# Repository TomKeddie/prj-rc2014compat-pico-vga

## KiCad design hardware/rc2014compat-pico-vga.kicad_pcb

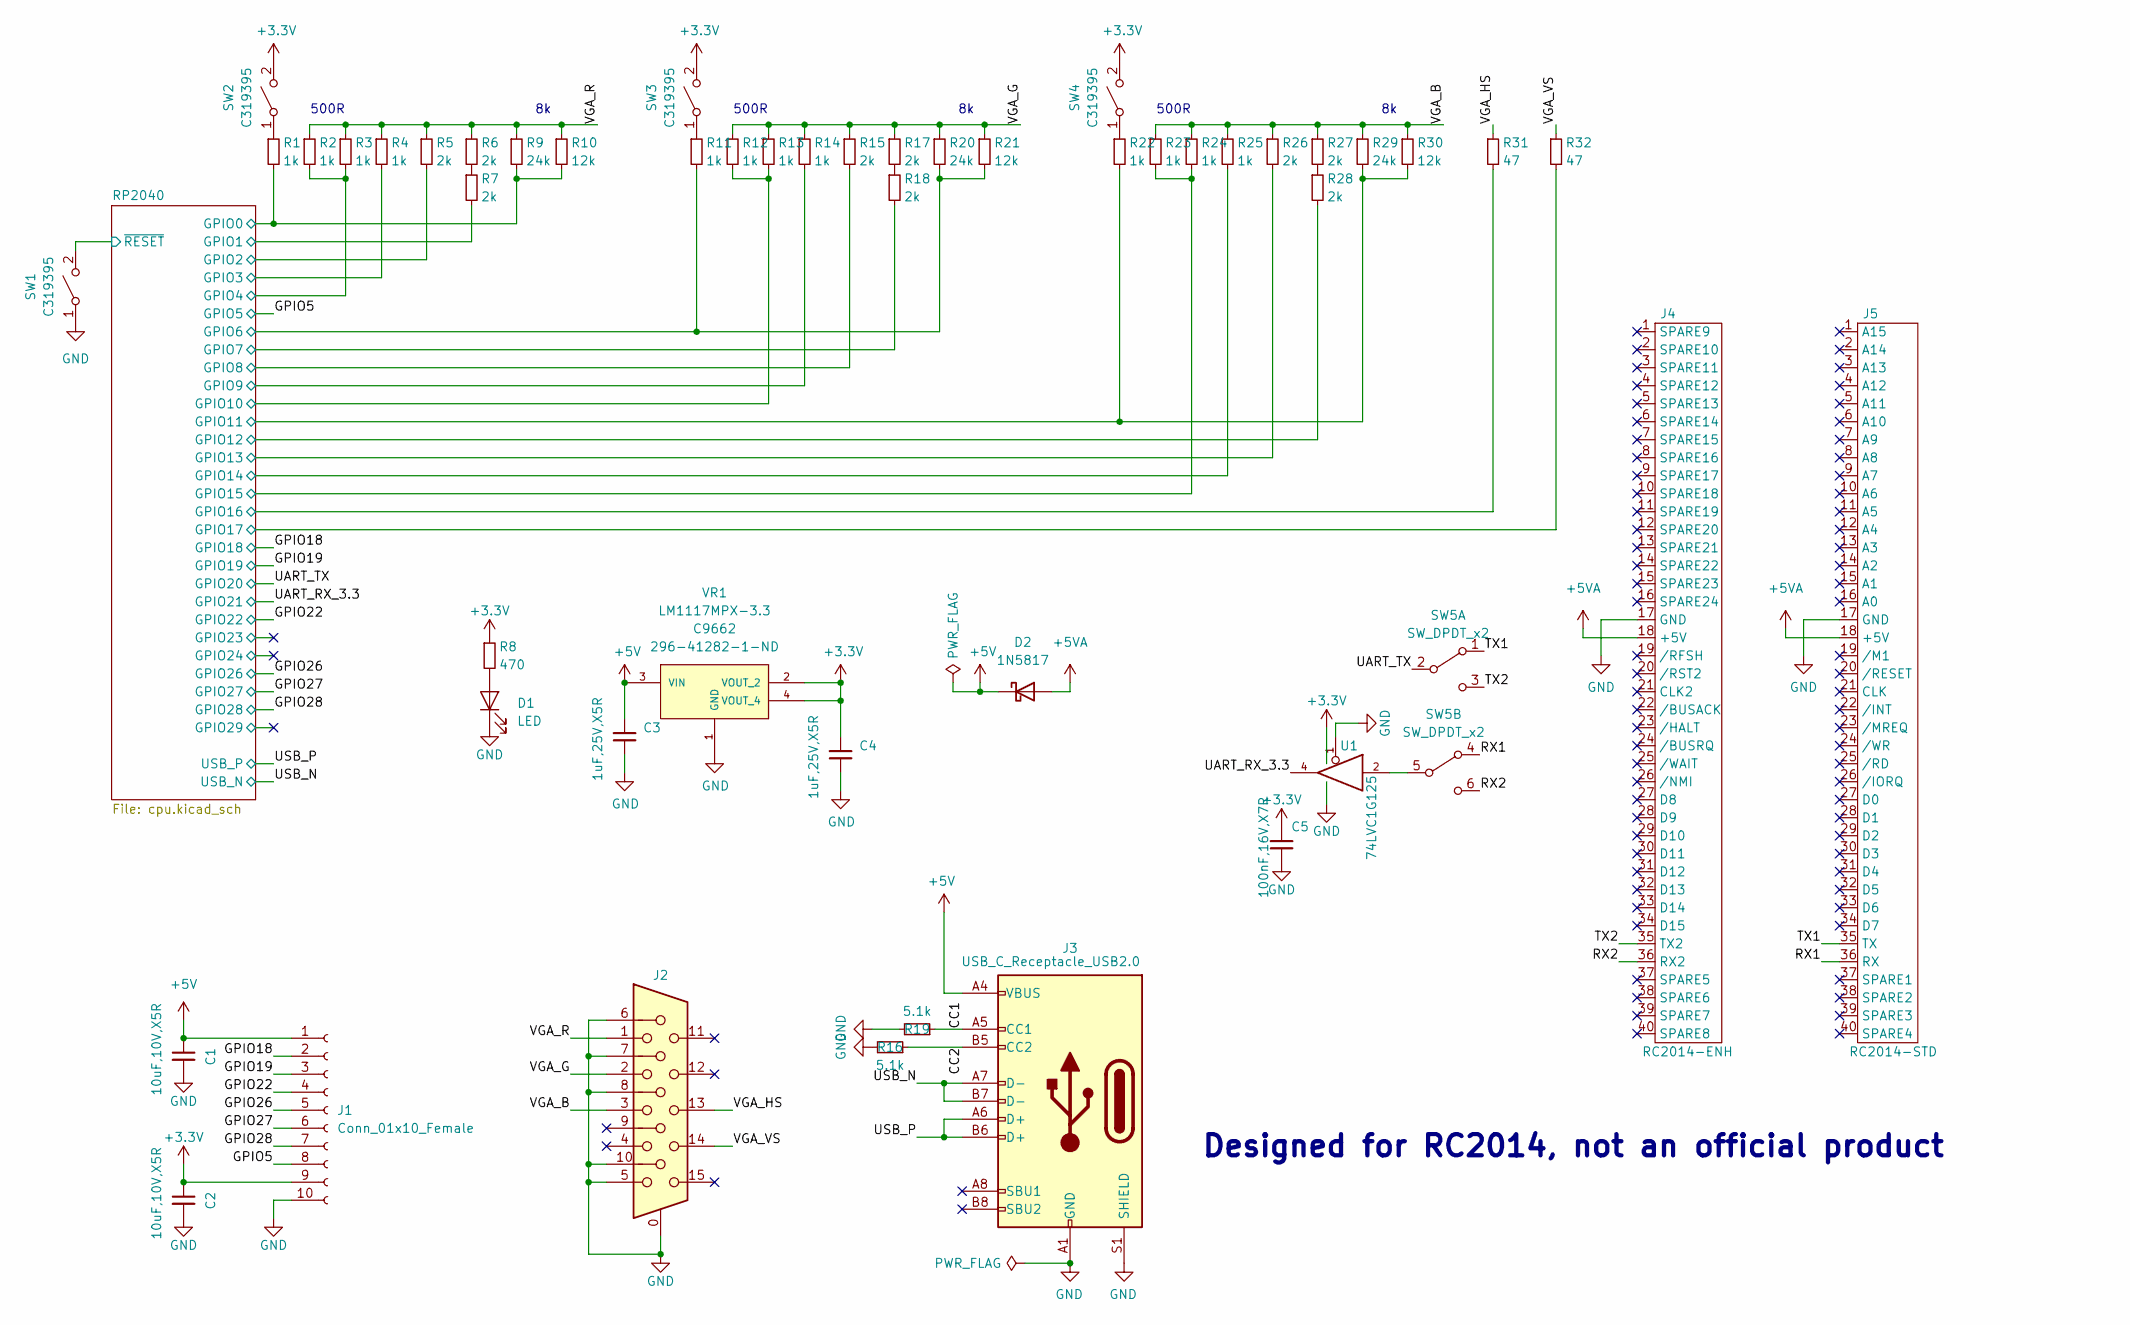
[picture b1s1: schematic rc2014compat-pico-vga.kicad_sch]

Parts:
C1, C2: 10uF,10V,X5R; C_0603_1608Metric; MFGPN CL10A106KP8NNNC; LCSC C19702
C3, C4: 1uF,25V,X5R; C_0402_1005Metric; MFGPN CL05A105KA5NQNC; LCSC C52923
C5: 100nF,16V,X7R; C_0402_1005Metric; MFGPN CL05B104KO5NNNC; LCSC C1525
D1: LED; LED_0603_1608Metric; LCSC C2286
D2: 1N5817; D_SOD-123; LCSC C727113
J1: Conn_01x10_Female; PinHeader_1x10_P2.54mm_Vertical
J2: DB15_Female_HighDensity_MountingHoles; DSUB-15-HD_Female_Horizontal_P2.29x1.98mm_EdgePinOffset3.03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; LCSC C711364
J3: USB_C_Receptacle_USB2.0; USB_C_Receptacle_GT-USB-7010; LCSC C709357
J4: RC2014-ENH; PinHeader_1x39_P2.54mm_Horizontal
J5: RC2014-STD; PinHeader_1x39_P2.54mm_Horizontal
R1, R2, R3, R4, R11, R12, R13, R14, R22, R23, R24, R25: 1k; R_0402_1005Metric; MFGPN 0402WGF1001TCE; LCSC C11702
R5, R6, R7, R15, R17, R18, R26, R27, R28: 2k; R_0402_1005Metric; MFGPN 0402WGF2001TCE; LCSC C4109
R8: 470; R_0402_1005Metric; MFGPN 0402WGF4700TCE; LCSC C25117
R9, R20, R29: 24k; R_0402_1005Metric; MFGPN 0402WGF2402TCE; LCSC C25769
R10, R21, R30: 12k; R_0402_1005Metric; MFGPN 0402WGF1202TCE; LCSC C25752
R16, R19: 5.1k; R_0402_1005Metric; MFGPN 0402WGF5101TCE; LCSC C25905
R31, R32: 47; R_0402_1005Metric; MFGPN 0402WGF470JTCE; LCSC C25118
SW1, SW2, SW3, SW4: C319395; SW_SPST_SMD_SIDE_C319395; LCSC C319395
SW5: SW_DPDT_x2; SW_DPDT_SMD; LCSC C381098
U1: 74LVC1G125; SOT-23-5
VR1: LM1117MPX-3.3; VREG_LM1117MPX-3.3; PARTREV O; LCSC C9662

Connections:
+3.3V: C2.1, C4.1, C5.1, J1.9, R8.1, SW2.2 (B), SW3.2 (B), SW4.2 (B), U1.5 (VCC), VR1.2 (VOUT_2), VR1.4 (VOUT_4); also elsewhere on the board
+5V: C1.1, C3.1, D2.1 (K), J1.1, J3.A4 (VBUS), J3.A9 (VBUS), J3.B4 (VBUS), J3.B9 (VBUS), VR1.3 (VIN)
+5VA: D2.2 (A), J4.18 (+5V), J5.18 (+5V)
/CC1: J3.A5 (CC1), R19.1
/CC2: J3.B5 (CC2), R16.1
/GPIO5: J1.8; also elsewhere on the board
/GPIO18: J1.2; also elsewhere on the board
/GPIO19: J1.3; also elsewhere on the board
/GPIO22: J1.4; also elsewhere on the board
/GPIO26: J1.5; also elsewhere on the board
/GPIO27: J1.6; also elsewhere on the board
/GPIO28: J1.7; also elsewhere on the board
/RP2040/GPIO0: R1.2, R9.2, R10.2; also elsewhere on the board
/RP2040/GPIO1: R7.2; also elsewhere on the board
/RP2040/GPIO2: R5.2; also elsewhere on the board
/RP2040/GPIO3: R4.2; also elsewhere on the board
/RP2040/GPIO4: R2.2, R3.2; also elsewhere on the board
/RP2040/GPIO6: R11.2, R20.2, R21.2; also elsewhere on the board
/RP2040/GPIO7: R18.2; also elsewhere on the board
/RP2040/GPIO8: R15.2; also elsewhere on the board
/RP2040/GPIO9: R14.2; also elsewhere on the board
/RP2040/GPIO10: R12.2, R13.2; also elsewhere on the board
/RP2040/GPIO11: R22.2, R29.2, R30.2; also elsewhere on the board
/RP2040/GPIO12: R28.2; also elsewhere on the board
/RP2040/GPIO13: R26.2; also elsewhere on the board
/RP2040/GPIO14: R25.2; also elsewhere on the board
/RP2040/GPIO15: R23.2, R24.2; also elsewhere on the board
/RP2040/GPIO16: R31.2; also elsewhere on the board
/RP2040/GPIO17: R32.2; also elsewhere on the board
/RP2040/~RESET: SW1.2 (B); also elsewhere on the board
/RX1: J5.36 (RX), SW5.4 (A)
/RX2: J4.36 (RX2), SW5.6 (C)
/TX1: J5.35 (TX), SW5.1 (A)
/TX2: J4.35 (TX2), SW5.3 (C)
/UART_RX_3.3: U1.4; also elsewhere on the board
/UART_TX: SW5.2 (B); also elsewhere on the board
/USB_N: J3.A7 (D-), J3.B7 (D-); also elsewhere on the board
/USB_P: J3.A6 (D+), J3.B6 (D+); also elsewhere on the board
/VGA_B: J2.3, R23.1, R24.1, R25.1, R26.1, R27.1, R29.1, R30.1
/VGA_G: J2.2, R12.1, R13.1, R14.1, R15.1, R17.1, R20.1, R21.1
/VGA_HS: J2.13, R31.1
/VGA_R: J2.1, R2.1, R3.1, R4.1, R5.1, R6.1, R9.1, R10.1
/VGA_VS: J2.14, R32.1
GND: C1.2, C2.2, C3.2, C4.2, C5.2, D1.1 (K), J1.10, J2.0, J2.5, J2.6, J2.7, J2.8, J2.10, J3.A1 (GND), J3.A12 (GND), J3.B1 (GND), J3.B12 (GND), J3.S1 (SHIELD), J4.17 (GND), J5.17 (GND), R16.2, R19.2, SW1.1 (A), U1.1, U1.3 (GND), VR1.1 (GND); also elsewhere on the board
unnamed: D1.2 (A), R8.2
unnamed: R1.1, SW2.1 (A)
unnamed: R6.2, R7.1
unnamed: R11.1, SW3.1 (A)
unnamed: R17.2, R18.1
unnamed: R22.1, SW4.1 (A)
unnamed: R27.2, R28.1
unnamed: SW5.5 (B), U1.2

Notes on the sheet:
500R
Designed for RC2014, not an official product

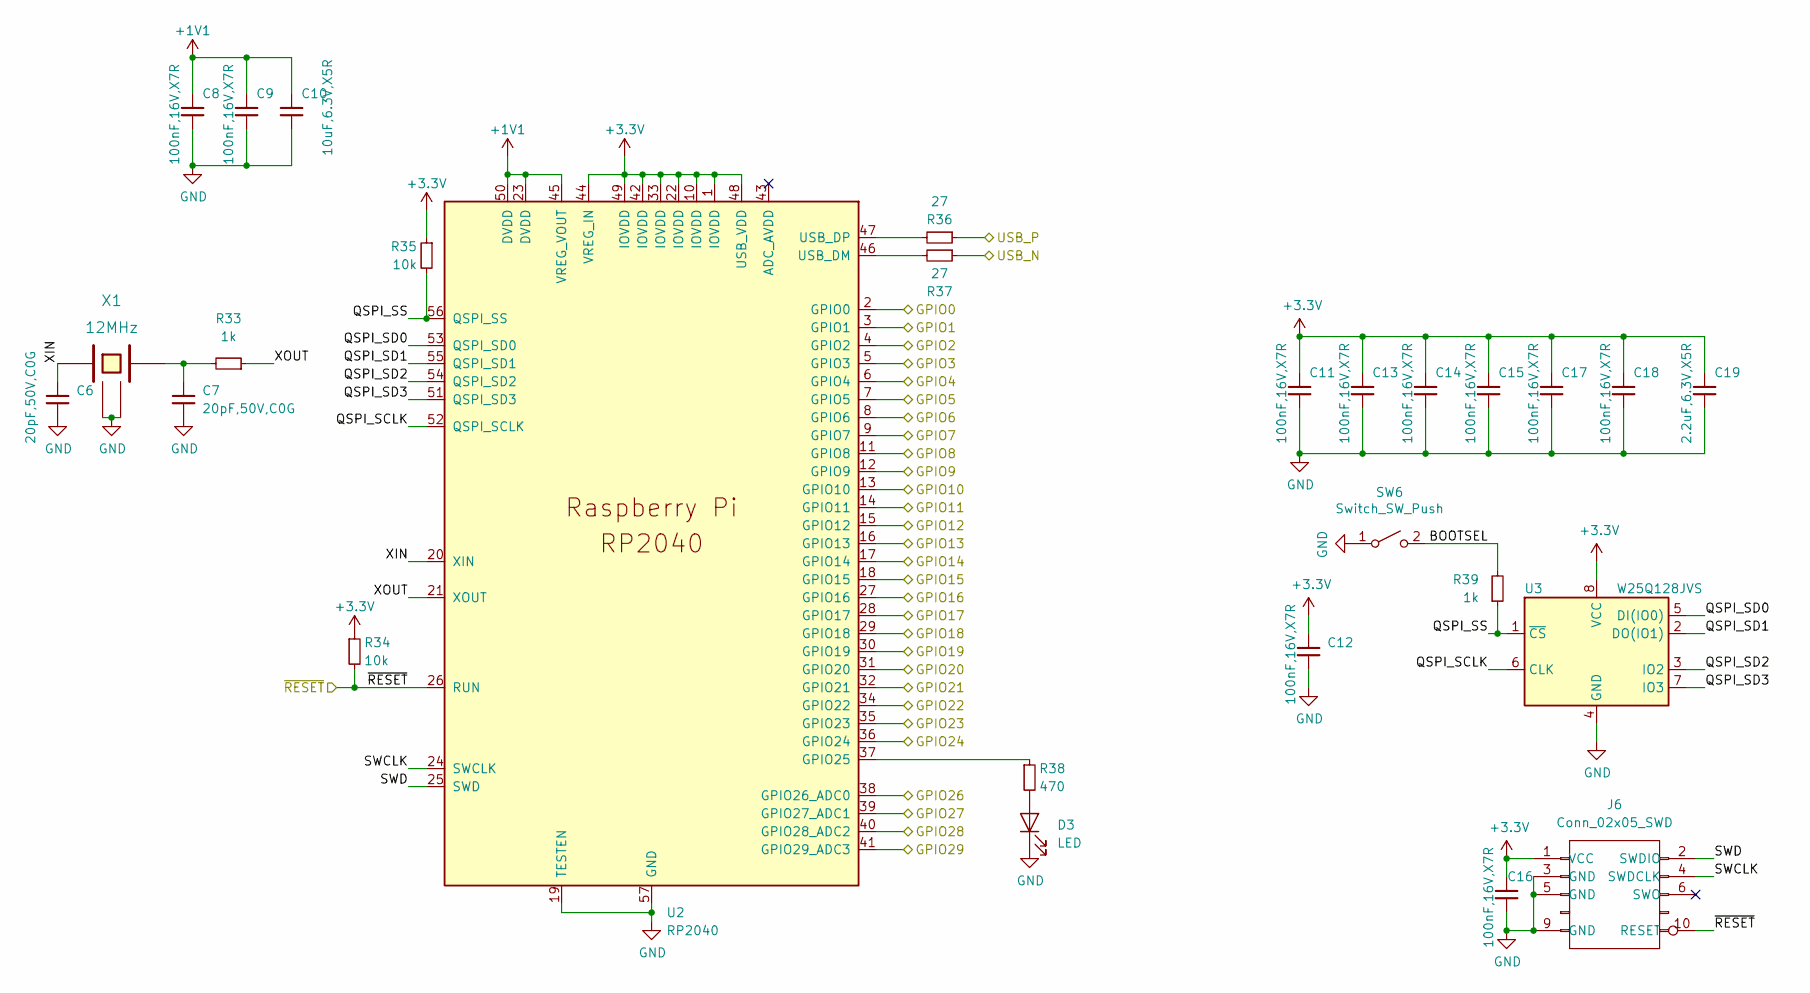
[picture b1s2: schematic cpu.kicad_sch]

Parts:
C6, C7: 20pF,50V,C0G; C_0402_1005Metric; MFGPN 0402CG200J500NT; LCSC C1554
C8, C9, C11, C12, C13, C14, C15, C16, C17, C18: 100nF,16V,X7R; C_0402_1005Metric; MFGPN CL05B104KO5NNNC; LCSC C1525
C10: 10uF,6.3V,X5R; C_0402_1005Metric; MFGPN CL05A106MQ5NUNC; LCSC C15525
C19: 2.2uF,6.3V,X5R; C_0402_1005Metric; MFGPN CL05A225MQ5NSNC; LCSC C12530
D3: LED; LED_0603_1608Metric; LCSC C2290
J6: Conn_02x05_SWD; FTSH-105-01-F-DV-K
R33, R39: 1k; R_0402_1005Metric; MFGPN 0402WGF1001TCE; LCSC C11702
R34, R35: 10k; R_0402_1005Metric; MFGPN 0402WGF1002TCE; LCSC C25744
R36, R37: 27; R_0603_1608Metric; MFGPN 0603WAF270JT5E; LCSC C25190
R38: 470; R_0402_1005Metric; MFGPN 0402WGF4700TCE; LCSC C25117
SW6: Switch_SW_Push; SW_SPST_SMD_SIDE_C319395; LCSC C319395
U2: RP2040; RP2040-QFN-56; LCSC C2040
U3: W25Q128JVS; SOIC-8_5.23x5.23mm_P1.27mm; LCSC C97521
X1: 12MHz; Crystal_SMD_3225-4Pin_3.2x2.5mm; LCSC C9002

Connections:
+1V1: C8.1, C9.1, C10.1, U2.23 (DVDD), U2.45 (VREG_VOUT), U2.50 (DVDD)
+3.3V: C11.1, C12.1, C13.1, C14.1, C15.1, C16.1, C17.1, C18.1, C19.1, J6.1 (VCC), R34.1, R35.1, U2.1 (IOVDD), U2.10 (IOVDD), U2.22 (IOVDD), U2.33 (IOVDD), U2.42 (IOVDD), U2.44 (VREG_IN), U2.48 (USB_VDD), U2.49 (IOVDD), U3.8 (VCC); also elsewhere on the board
/GPIO5: U2.7 (GPIO5); also elsewhere on the board
/GPIO18: U2.29 (GPIO18); also elsewhere on the board
/GPIO19: U2.30 (GPIO19); also elsewhere on the board
/GPIO22: U2.34 (GPIO22); also elsewhere on the board
/GPIO26: U2.38 (GPIO26_ADC0); also elsewhere on the board
/GPIO27: U2.39 (GPIO27_ADC1); also elsewhere on the board
/GPIO28: U2.40 (GPIO28_ADC2); also elsewhere on the board
/RP2040/BOOTSEL: R39.2, SW6.2 (B)
/RP2040/GPIO0: U2.2 (GPIO0); also elsewhere on the board
/RP2040/GPIO1: U2.3 (GPIO1); also elsewhere on the board
/RP2040/GPIO2: U2.4 (GPIO2); also elsewhere on the board
/RP2040/GPIO3: U2.5 (GPIO3); also elsewhere on the board
/RP2040/GPIO4: U2.6 (GPIO4); also elsewhere on the board
/RP2040/GPIO6: U2.8 (GPIO6); also elsewhere on the board
/RP2040/GPIO7: U2.9 (GPIO7); also elsewhere on the board
/RP2040/GPIO8: U2.11 (GPIO8); also elsewhere on the board
/RP2040/GPIO9: U2.12 (GPIO9); also elsewhere on the board
/RP2040/GPIO10: U2.13 (GPIO10); also elsewhere on the board
/RP2040/GPIO11: U2.14 (GPIO11); also elsewhere on the board
/RP2040/GPIO12: U2.15 (GPIO12); also elsewhere on the board
/RP2040/GPIO13: U2.16 (GPIO13); also elsewhere on the board
/RP2040/GPIO14: U2.17 (GPIO14); also elsewhere on the board
/RP2040/GPIO15: U2.18 (GPIO15); also elsewhere on the board
/RP2040/GPIO16: U2.27 (GPIO16); also elsewhere on the board
/RP2040/GPIO17: U2.28 (GPIO17); also elsewhere on the board
/RP2040/GPIO23: U2.35 (GPIO23)
/RP2040/GPIO24: U2.36 (GPIO24)
/RP2040/GPIO29: U2.41 (GPIO29_ADC3)
/RP2040/QSPI_SCLK: U2.52 (QSPI_SCLK), U3.6 (CLK)
/RP2040/QSPI_SD0: U2.53 (QSPI_SD0), U3.5 (DI(IO0))
/RP2040/QSPI_SD1: U2.55 (QSPI_SD1), U3.2 (DO(IO1))
/RP2040/QSPI_SD2: U2.54 (QSPI_SD2), U3.3 (IO2)
/RP2040/QSPI_SD3: U2.51 (QSPI_SD3), U3.7 (IO3)
/RP2040/QSPI_SS: R35.2, R39.1, U2.56 (QSPI_SS), U3.1 (~CS)
/RP2040/SWCLK: J6.4 (SWDCLK), U2.24 (SWCLK)
/RP2040/SWD: J6.2 (SWDIO), U2.25 (SWD)
/RP2040/XIN: C6.1, U2.20 (XIN), X1.1
/RP2040/XOUT: R33.1, U2.21 (XOUT)
/RP2040/~RESET: J6.10 (RESET), R34.2, U2.26 (RUN); also elsewhere on the board
/UART_RX_3.3: U2.32 (GPIO21); also elsewhere on the board
/UART_TX: U2.31 (GPIO20); also elsewhere on the board
/USB_N: R37.1; also elsewhere on the board
/USB_P: R36.1; also elsewhere on the board
GND: C6.2, C7.2, C8.2, C9.2, C10.2, C11.2, C12.2, C13.2, C14.2, C15.2, C16.2, C17.2, C18.2, C19.2, D3.1 (K), J6.3 (GND), J6.5 (GND), J6.9 (GND), SW6.1 (A), U2.19 (TESTEN), U2.57 (GND), U3.4 (GND), X1.2 (GND), X1.4 (GND); also elsewhere on the board
unnamed: C7.1, R33.2, X1.3
unnamed: D3.2 (A), R38.2
unnamed: R36.2, U2.47 (USB_DP)
unnamed: R37.2, U2.46 (USB_DM)
unnamed: R38.1, U2.37 (GPIO25)

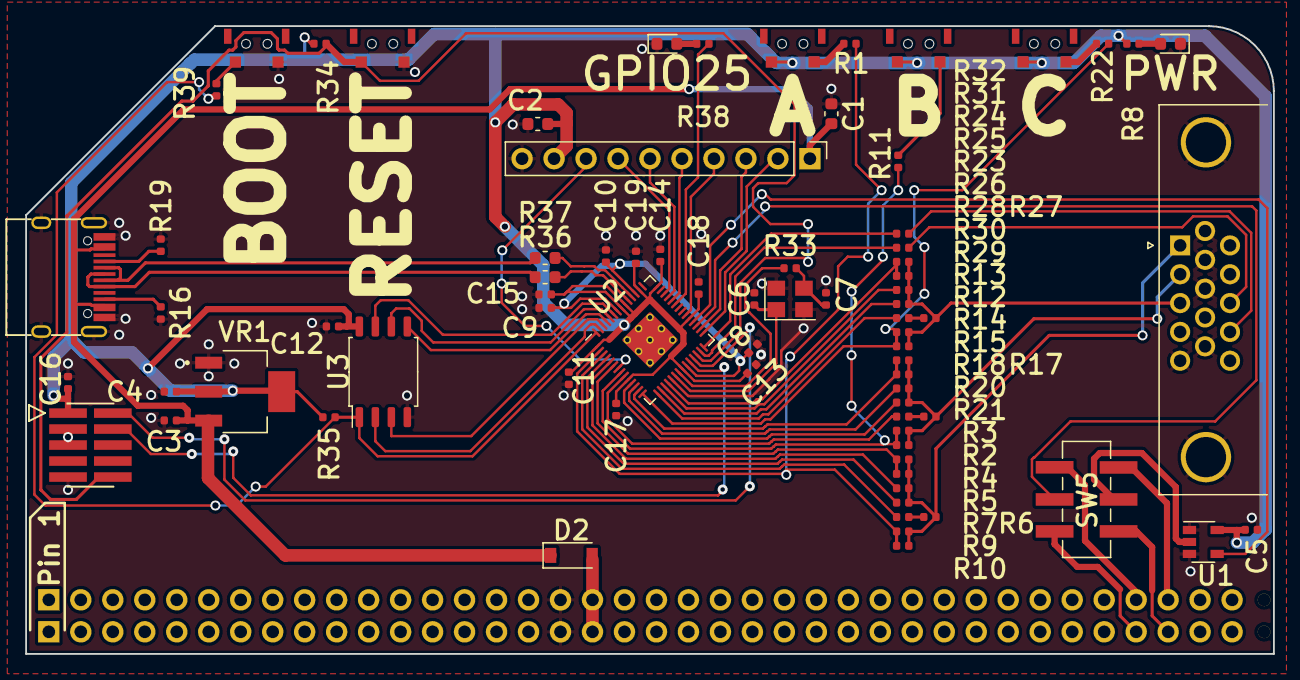
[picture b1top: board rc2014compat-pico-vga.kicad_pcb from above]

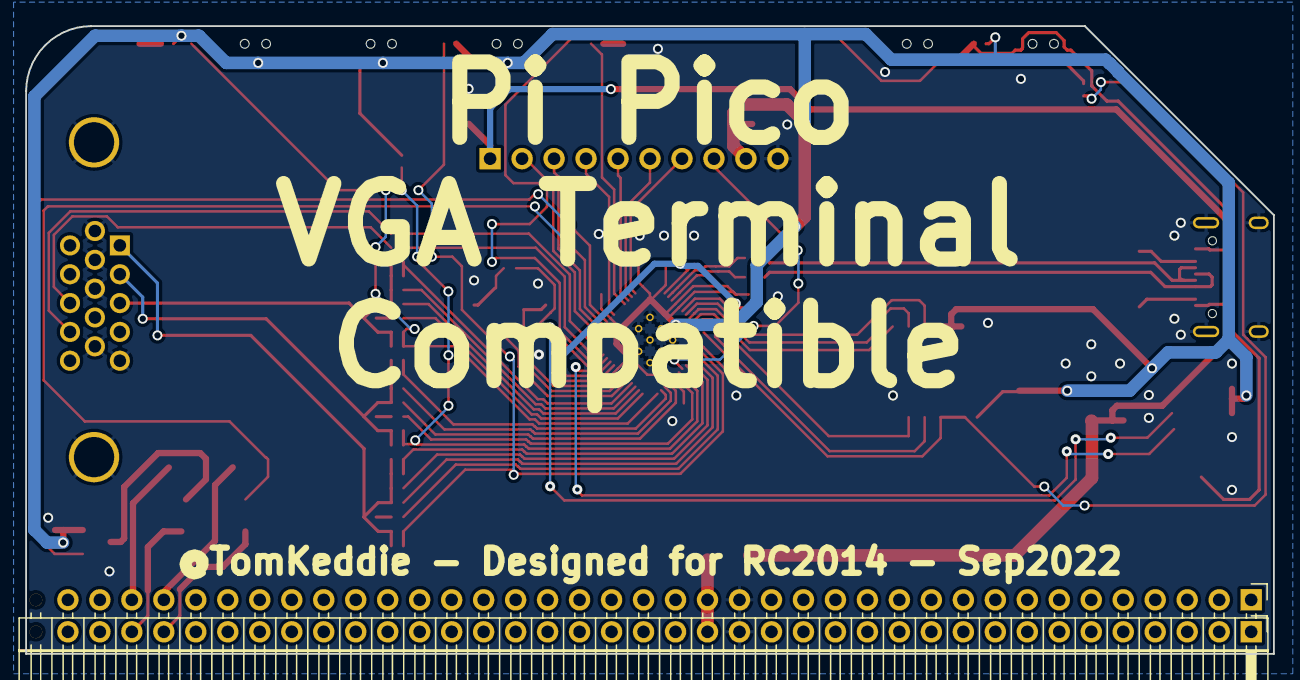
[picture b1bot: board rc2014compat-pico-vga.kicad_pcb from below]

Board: 2 copper layers, 99.1 x 49.9 mm, 78 parts (2 on the bottom side), 69 nets.

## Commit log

2022-09-23 rc2014compat-pico-vga: pic vga clone designed for RC2014
2022-09-25 hardware: pcb routing complete
2022-09-25 hardware: add jlcpcb assembly files
2022-09-26 hardware: Sep2022 as submitted
2023-01-23 hardware: as submitted to jlcpcb

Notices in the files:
parts and their libraries:
Copyright 2016 Accelerated Designs. All rights reserved.
